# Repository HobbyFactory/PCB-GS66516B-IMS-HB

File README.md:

# PCB-GS66516B-IMS-HB
GaN (GS66516B) Half-Bridge designed on a metal substrate printed circuit board, including the gate drivers.

All data included, designed in free tool KiCad. For more details check article:
Efficiency optimization of totem pole PFC with Gallium Nitride semiconductors (doi:10.15199/48.2021.06.07)

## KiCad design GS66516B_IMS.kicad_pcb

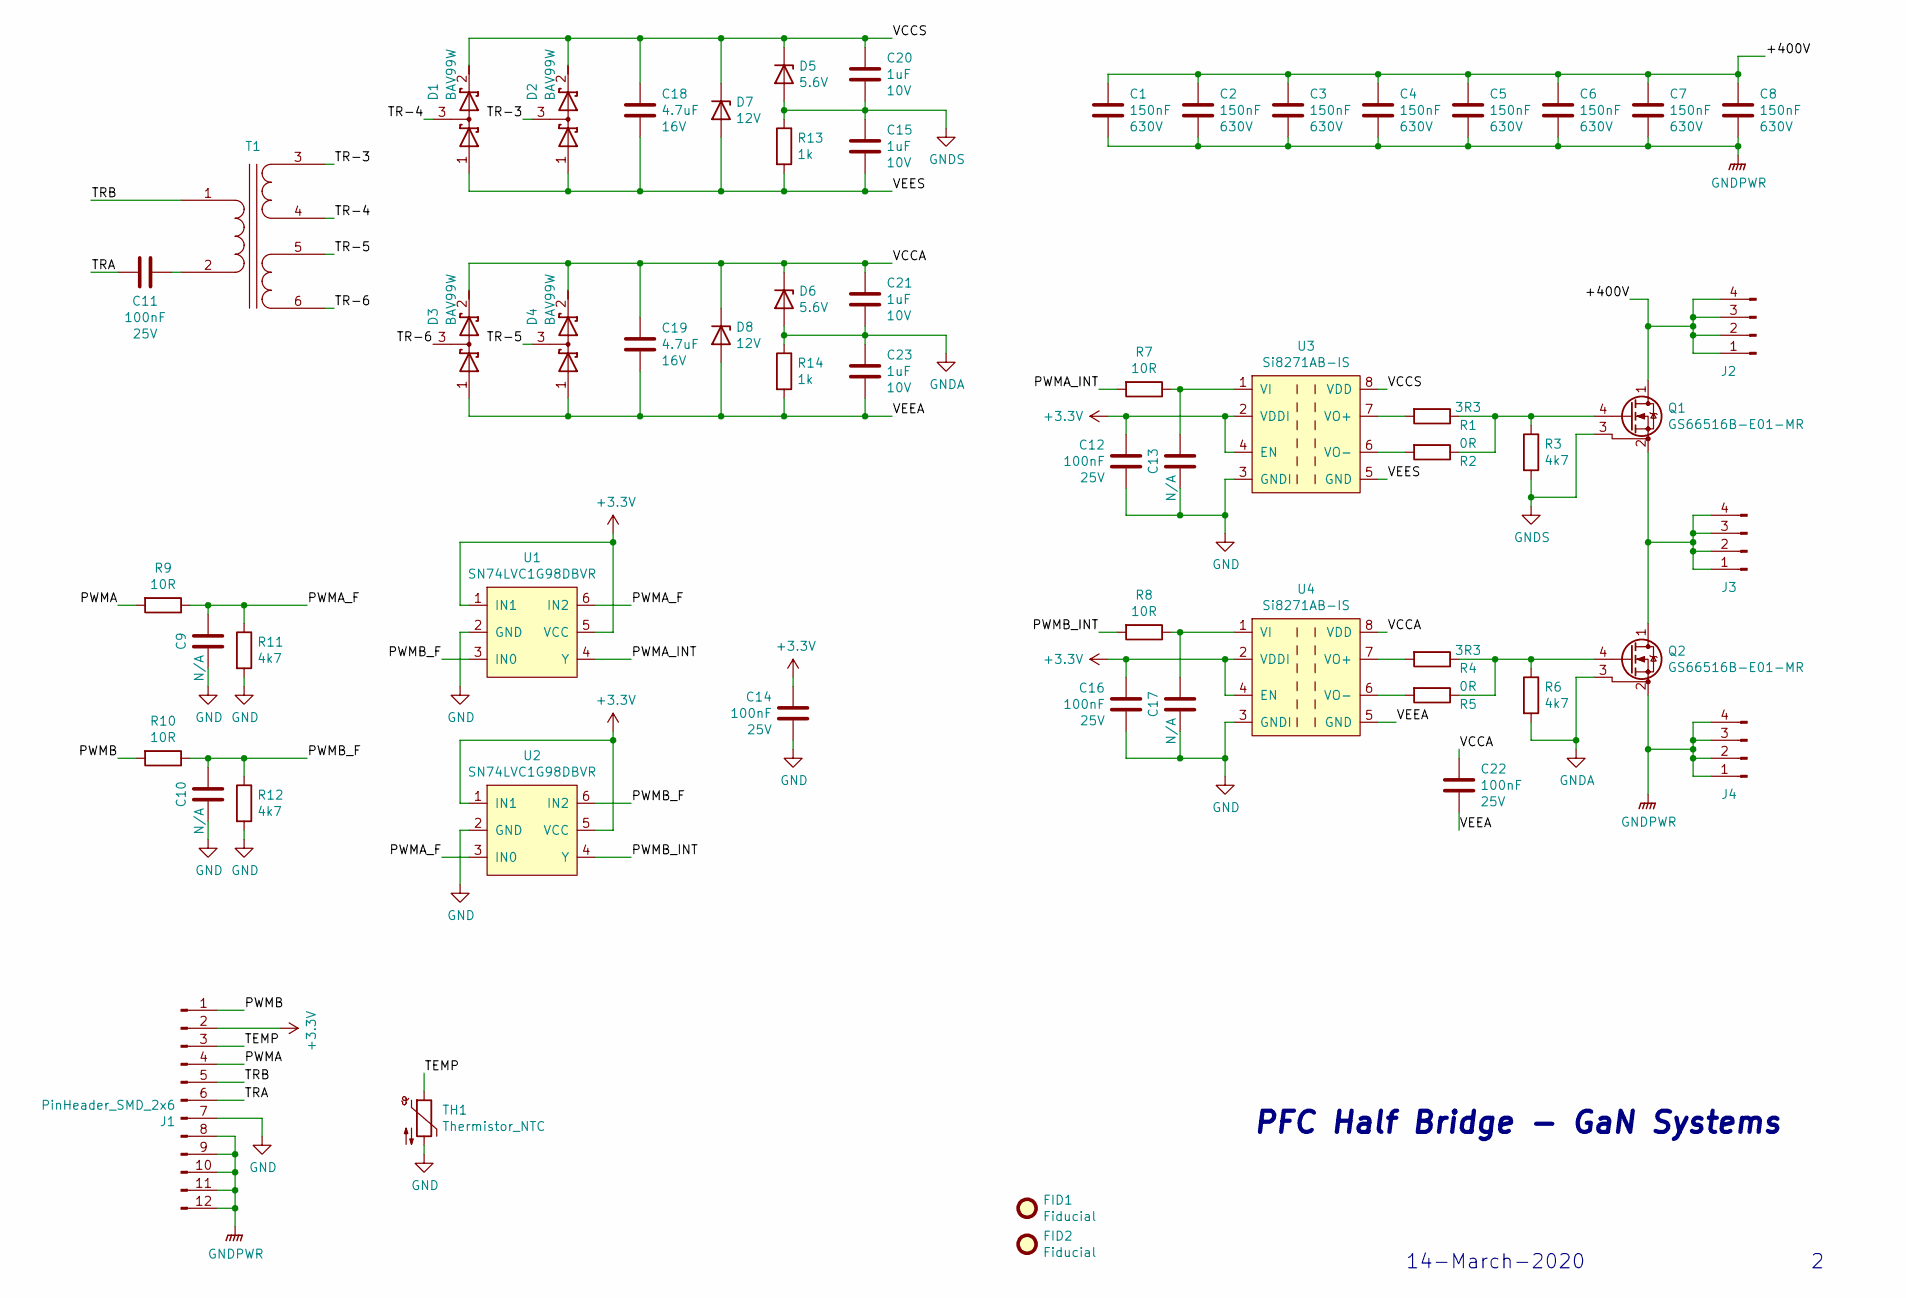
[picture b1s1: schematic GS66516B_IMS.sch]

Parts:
C1, C2, C3, C4, C5, C6, C7, C8: 150nF; C_1210_3225Metric; Voltage 630V
C9, C10, C13, C17: N/A; C_0402_1005Metric
C11, C12, C14, C16, C22: 100nF; C_0402_1005Metric; Voltage 25V
C15, C20, C21, C23: 1uF; C_0402_1005Metric; Voltage 10V
C18, C19: 4.7uF; C_0805_2012Metric; Voltage 16V
D1, D2, D3, D4: BAV99W; SOT-323_SC-70
D5, D6: 5.6V; D_SOD-523; Voltage 5.6V
D7: 12V; D_SOD-523; Voltage 12V
D8: 12V; D_SOD-523
FID1, FID2: Fiducial; Fiducial_0.5mm_Mask1mm
J1: PinHeader_SMD_2x6; PinHeader_SMD_Horizontal_2.00mm_2x6
J2, J3, J4: PinHeader_SMD_1x4; PinHeader_SMD_Horizontal_2.00mm_1x4_Modified
Q1, Q2: GS66516B-E01-MR; Transistor_GaN_GS66516B
R1, R4: 3R3; R_0402_1005Metric
R2, R5: 0R; R_0402_1005Metric
R3, R6, R11, R12: 4k7; R_0402_1005Metric
R7, R8, R9, R10: 10R; R_0402_1005Metric
R13, R14: 1k; R_0402_1005Metric
T1: Transformer_BPS_WCT.00171
TH1: Thermistor_NTC; R_0603_1608Metric
U1, U2: SN74LVC1G98DBVR; SOT-23-6
U3, U4: Si8271AB-IS; SOIC-8_3.9x4.9mm_P1.27mm

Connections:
+3V3: C12.1, C14.1, C16.1, J1.2, U1.1 (IN1), U1.5 (VCC), U2.1 (IN1), U2.5 (VCC), U3.2 (VDDI), U3.4 (EN), U4.2 (VDDI), U4.4 (EN)
/+400V: C1.1, C2.1, C3.1, C4.1, C5.1, C6.1, C7.1, C8.2, J2.1, J2.2, J2.3, J2.4, Q1.1 (D)
/PWMA: J1.4, R9.2
/PWMA_F: C9.1, R9.1, R11.1, U1.6 (IN2), U2.3 (IN0)
/PWMA_INT: R7.2, U1.4 (Y)
/PWMB: J1.1, R10.2
/PWMB_F: C10.1, R10.1, R12.1, U1.3 (IN0), U2.6 (IN2)
/PWMB_INT: R8.2, U2.4 (Y)
/TEMP: J1.3, TH1.1
/TR-3: D2.3 (common), T1.3 (SA)
/TR-4: D1.3 (common), T1.4 (SB)
/TR-5: D4.3 (common), T1.5 (SC)
/TR-6: D3.3 (common), T1.6 (SD)
/TRA: C11.2, J1.6
/TRB: J1.5, T1.1 (AA)
/VCCA: C19.1, C21.1, C22.1, D3.2 (K), D4.2 (K), D6.1 (K), D8.1 (K), U4.8 (VDD)
/VCCS: C18.1, C20.1, D1.2 (K), D2.2 (K), D5.1 (K), D7.1 (K), U3.8 (VDD)
/VEEA: C19.2, C22.2, C23.2, D3.1 (A), D4.1 (A), D8.2 (A), R14.2, U4.5 (GND)
/VEES: C15.2, C18.2, D1.1 (A), D2.1 (A), D7.2 (A), R13.2, U3.5 (GND)
GND: C9.2, C10.2, C12.2, C13.2, C14.2, C16.2, C17.2, J1.7, R11.2, R12.2, TH1.2, U1.2 (GND), U2.2 (GND), U3.3 (GNDI), U4.3 (GNDI)
GNDA: C21.2, C23.1, D6.2 (A), Q2.3 (DS), R6.2, R14.1
GNDPWR: C1.2, C2.2, C3.2, C4.2, C5.2, C6.2, C7.2, C8.1, J1.8, J1.9, J1.10, J1.11, J1.12, J4.1, J4.2, J4.3, J4.4, Q2.2 (S)
GNDS: C15.1, C20.2, D5.2 (A), Q1.3 (DS), R3.2, R13.1
unnamed: C11.1, T1.2 (AB)
unnamed: C13.1, R7.1, U3.1 (VI)
unnamed: C17.1, R8.1, U4.1 (VI)
unnamed: J3.1, J3.2, J3.3, J3.4, Q1.2 (S), Q2.1 (D)
unnamed: Q1.4 (G), R1.1, R2.1, R3.1
unnamed: Q2.4 (G), R4.1, R5.1, R6.1
unnamed: R1.2, U3.7 (VO+)
unnamed: R2.2, U3.6 (VO-)
unnamed: R4.2, U4.7 (VO+)
unnamed: R5.2, U4.6 (VO-)

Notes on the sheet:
PFC Half Bridge - GaN Systems
14-March-2020

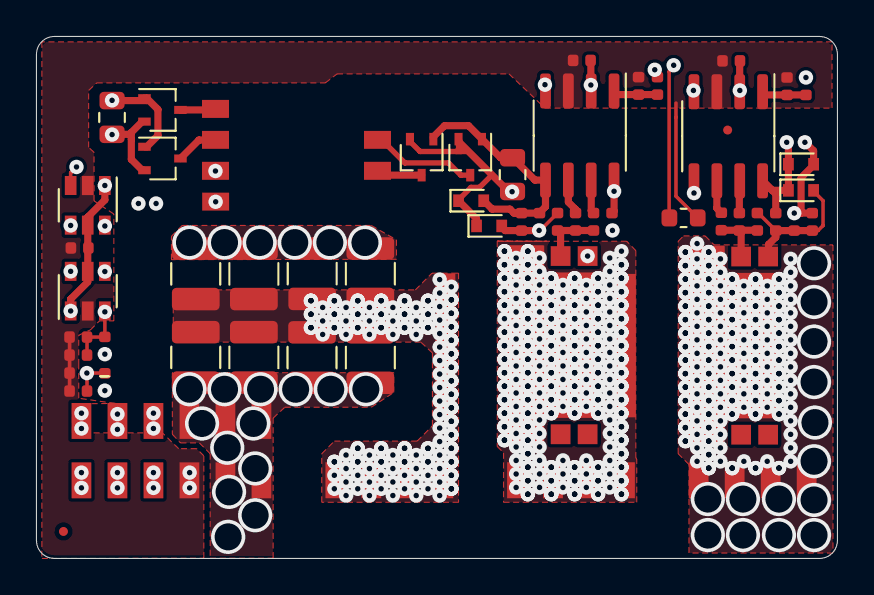
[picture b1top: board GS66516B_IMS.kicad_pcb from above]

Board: 4 copper layers, 44.5 x 29.0 mm, 59 parts (0 on the bottom side), 33 nets.

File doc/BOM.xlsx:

Item | Qty | Reference(s) | Value
1 | 8 | C1, C2, C3, C4, C5, C6, C7, C8 | 150nF/630V
2 | 4 | C9, C10, C13, C17 | N/A
3 | 5 | C11, C12, C14, C16, C22 | 100nF
4 | 4 | C15, C20, C21, C23 | 1uF
5 | 2 | C18, C19 | 4.7uF
6 | 4 | D1, D2, D3, D4 | BAV99W
7 | 2 | D5, D6 | 5.6V
8 | 2 | D7, D8 | 12V
9 | 3 | FID1, FID2, FID3 | Fiducial
10 | 5 | H1, H2, H3, H4, H5 | Panel mounting hole
11 | 1 | J1 | PinHeader_SMD_2x6
12 | 3 | J2, J3, J4 | PinHeader_SMD_1x4
13 | 2 | Q1, Q2 | GS66516B-E01-MR
14 | 6 | R1, R4, R7, R8, R9, R10 | 10R
15 | 2 | R2, R5 | 2R2
16 | 4 | R3, R6, R11, R12 | 4k7
17 | 2 | R13, R14 | 1k
18 | 1 | T1 | WCT.00171
19 | 1 | TH1 | Thermistor_NTC
20 | 2 | U1, U2 | SN74LVC1G98DBVR
21 | 2 | U3, U4 | Si8271AB-IS

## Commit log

2021-04-05 reduced size of picture
2021-04-05 picture in svg
2021-04-05 Update README.md
    finaly fixed picture...
2021-04-05 all in
2021-12-04 doc changes
